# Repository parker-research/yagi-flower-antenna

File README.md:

# yagi-flower-antenna

A group of UHF yagi antennas, arranged in a flower pattern and connected with a SP8T RF switch, to enable coarse beam direction control (like an antenna rotator, but solid-state).

The technical name for this not-all-that-novel approach is "faceted/switched-element array".

## Status

In development. Expected completion: 2026-12-01.

## Parts

1. Antennas (6x yagi antennas, approx. 7 dBi each)
2. Structural mount for antennas (see [`mechanical/`](mechanical/README.md))
3. SP8T RF switch PCB
    - Microcontroller
    - SP8T RF switch IC (SKY13418)
    - LNAs between each antenna port and the RF switch
    - SMA ports to each antenna + common
    - 3D-printed enclosure (see [`mechanical/`](mechanical/README.md))
4. Firmware for PCB microcontroller, masquerading as an antenna rotator (see [`firmware/`](firmware/README.md))
5. Cables to each antenna

## Why?

Satellite tracking works best with a directional antenna: less ambient noise/interference, and higher gain.

However, mechanical antenna rotators are expensive and wear out over time. They require zeroing/calibration, especially after power outages. There are no high-quality open source/DIY designs available. Cheap rotators (e.g., AntRunner) fail in weatherproofing.

This project aims to solve these problems by providing a low-cost, high-quality, open source/DIY, solid-state replacement for a traditional mechanical antenna rotator.

Consider an antenna being deployed in a remote location, like the arctic. As far as I can tell, this yagi flower antenna is ideal for such a deployment. And, an omnidirectional antenna might be almost as much work to build as this project is.

## Features

- Downlink-only
- Presents itself as a traditional antenna rotator, ensuring compatibility with existing antenna rotator software (e.g., SatNOGS Client, GPredict)
- Solid-state (no moving parts) adds reliability and durability for harsh environments

## Related Projects

### Research Papers

- "Concept of 3D Antenna Array for Sub-GHz Rotator-Less Small Satellite Ground Stations and Advanced IoT Gateways": https://www.mdpi.com/2673-4001/6/4/92 / https://doi.org/10.3390/telecom6040092

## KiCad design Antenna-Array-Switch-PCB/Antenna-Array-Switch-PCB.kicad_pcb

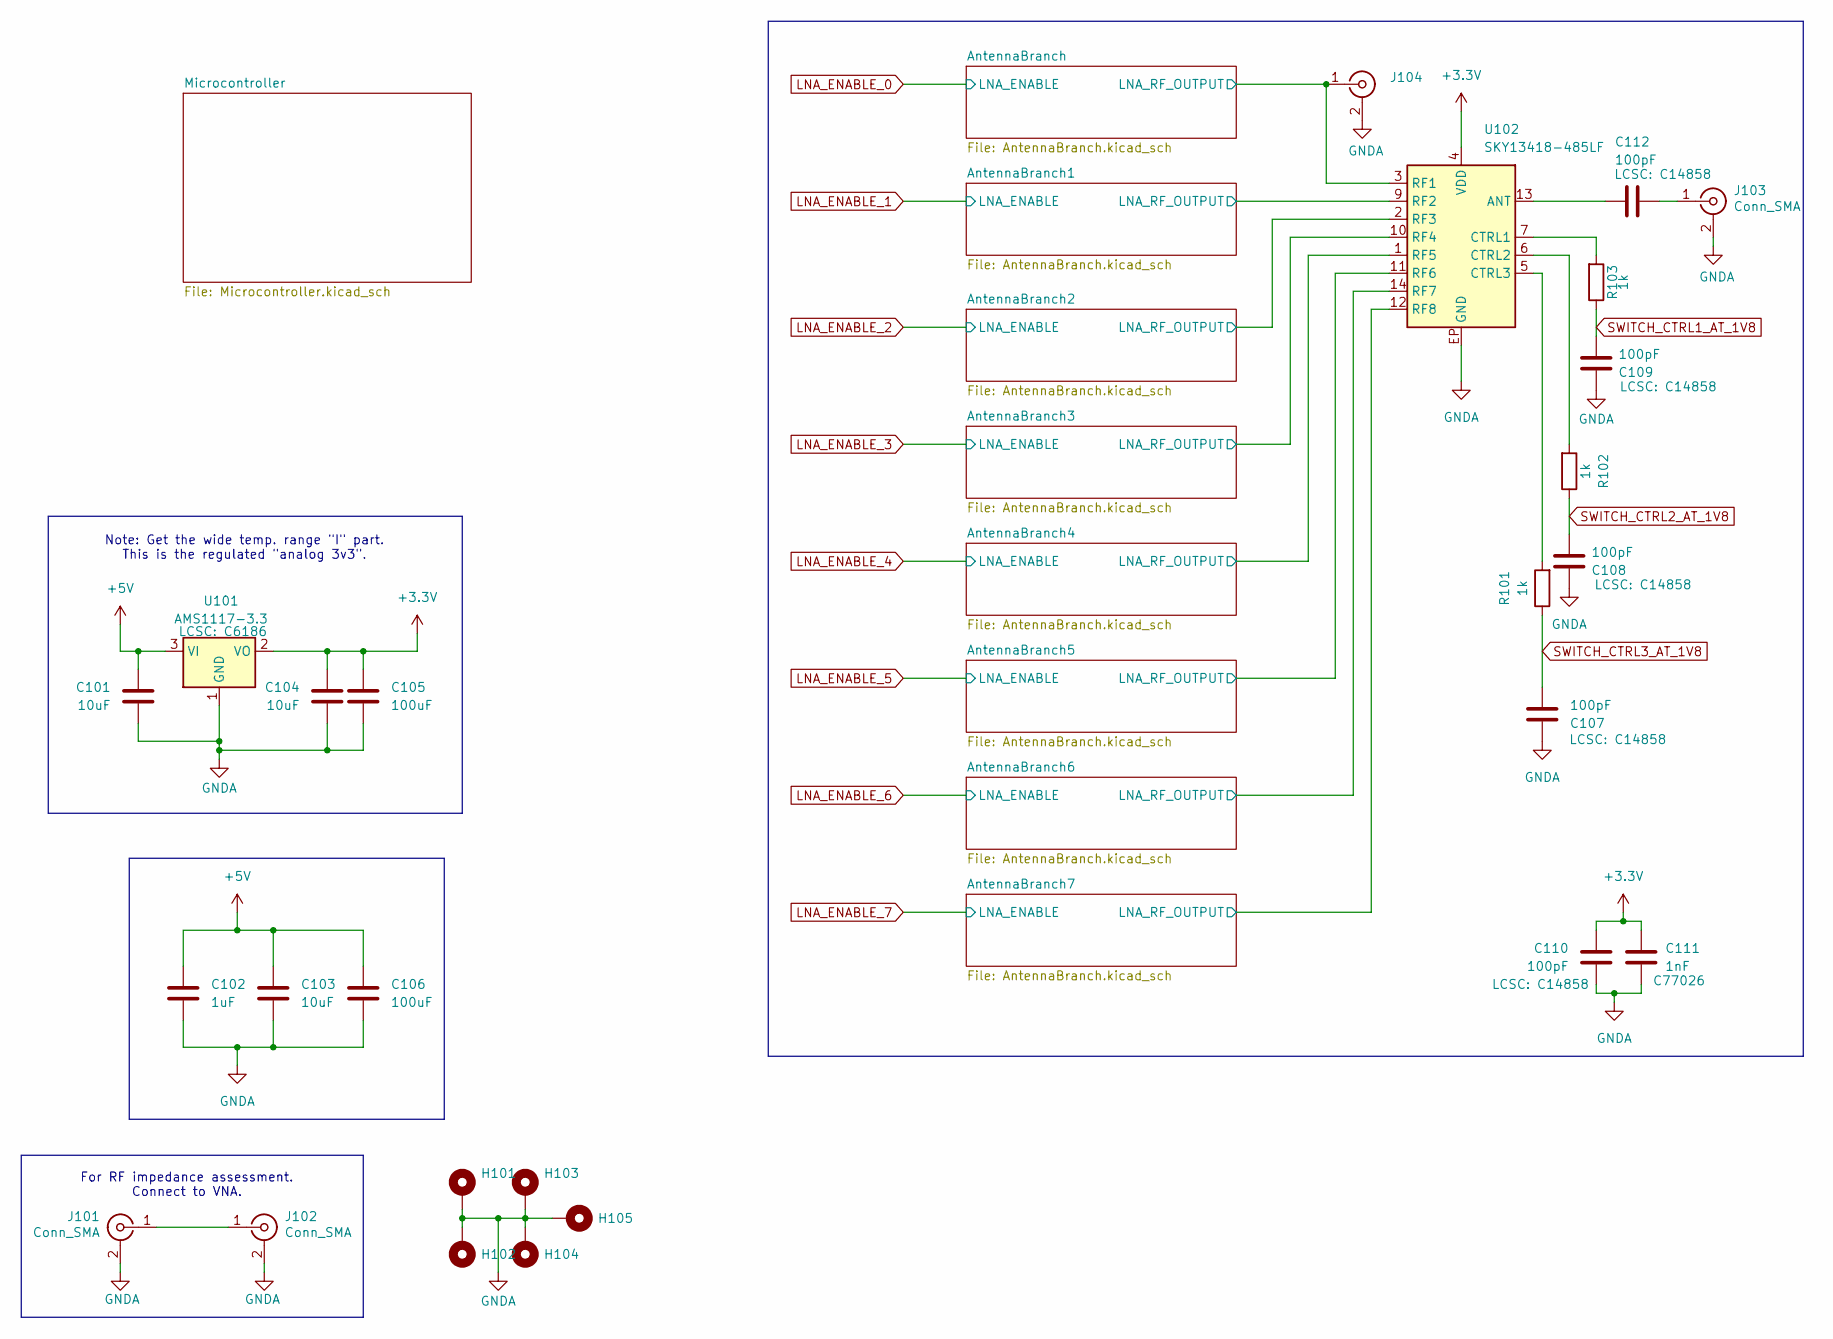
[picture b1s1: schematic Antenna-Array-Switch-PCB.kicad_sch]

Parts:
C101, C103, C104: 10uF; C_1206_3216Metric_Pad1.33x1.80mm_HandSolder
C102: 1uF; C_0603_1608Metric_Pad1.08x0.95mm_HandSolder
C105, C106: 100uF; C_1206_3216Metric_Pad1.33x1.80mm_HandSolder
C107, C108, C109, C110, C112: 100pF; C_0603_1608Metric_Pad1.08x0.95mm_HandSolder; LCSC C14858
C111: 1nF; C_0603_1608Metric_Pad1.08x0.95mm_HandSolder; LCSC C77026
H101, H102, H103, H104, H105: MountingHole_Pad; MountingHole_3.2mm_M3_Pad
J101, J102, J103: Conn_SMA; SMA_Amphenol_901-144_Vertical
J104: Conn_Coaxial; SMA_Amphenol_901-144_Vertical
R101, R102, R103: 1k; R_0603_1608Metric_Pad0.98x0.95mm_HandSolder
U101: AMS1117-3.3; SOT-223-3_TabPin2; LCSC C6186
U102: SKY13418-485LF; Skyworks_QFN-14-1EP_2x2mm_SKY13418_Handsolder; LCSC C150871

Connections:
+3.3V: C104.1, C105.1, C110.2, C111.2, U101.2 (VO), U102.4 (VDD)
+5V: C101.1, C102.1, C103.1, C106.1, U101.3 (VI); also elsewhere on the board
/AntennaBranch1/LNA_RF_OUTPUT: U102.9 (RF2); also elsewhere on the board
/AntennaBranch2/LNA_RF_OUTPUT: U102.2 (RF3); also elsewhere on the board
/AntennaBranch3/LNA_RF_OUTPUT: U102.10 (RF4); also elsewhere on the board
/AntennaBranch4/LNA_RF_OUTPUT: U102.1 (RF5); also elsewhere on the board
/AntennaBranch5/LNA_RF_OUTPUT: U102.11 (RF6); also elsewhere on the board
/AntennaBranch6/LNA_RF_OUTPUT: U102.14 (RF7); also elsewhere on the board
/AntennaBranch7/LNA_RF_OUTPUT: U102.12 (RF8); also elsewhere on the board
/AntennaBranch/LNA_RF_OUTPUT: J104.1 (In), U102.3 (RF1); also elsewhere on the board
GNDA: C101.2, C102.2, C103.2, C104.2, C105.2, C106.2, C107.2, C108.2, C109.2, C110.1, C111.1, H101.1 (1_1), H102.1 (1_1), H103.1 (1_1), H104.1 (1_1), H105.1 (1_1), J101.2 (Ext), J102.2 (Ext), J103.2 (Ext), J104.2 (Ext), U101.1 (GND), U102.EP (GND); also elsewhere on the board
unnamed: J101.1 (In), J102.1 (In)
unnamed: C112.1, J103.1 (In)
unnamed: C112.2, U102.13 (ANT)
unnamed: R103.2, U102.7 (CTRL1)
unnamed: R102.2, U102.6 (CTRL2)
unnamed: R101.2, U102.5 (CTRL3)
SWITCH_CTRL1_AT_1V8: C109.1, R103.1; also elsewhere on the board
SWITCH_CTRL2_AT_1V8: C108.1, R102.1; also elsewhere on the board
SWITCH_CTRL3_AT_1V8: C107.1, R101.1; also elsewhere on the board

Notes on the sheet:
For RF impedance assessment. Connect to VNA.
Note: Get the wide temp. range "I" part. This is the regulated "analog 3v3".

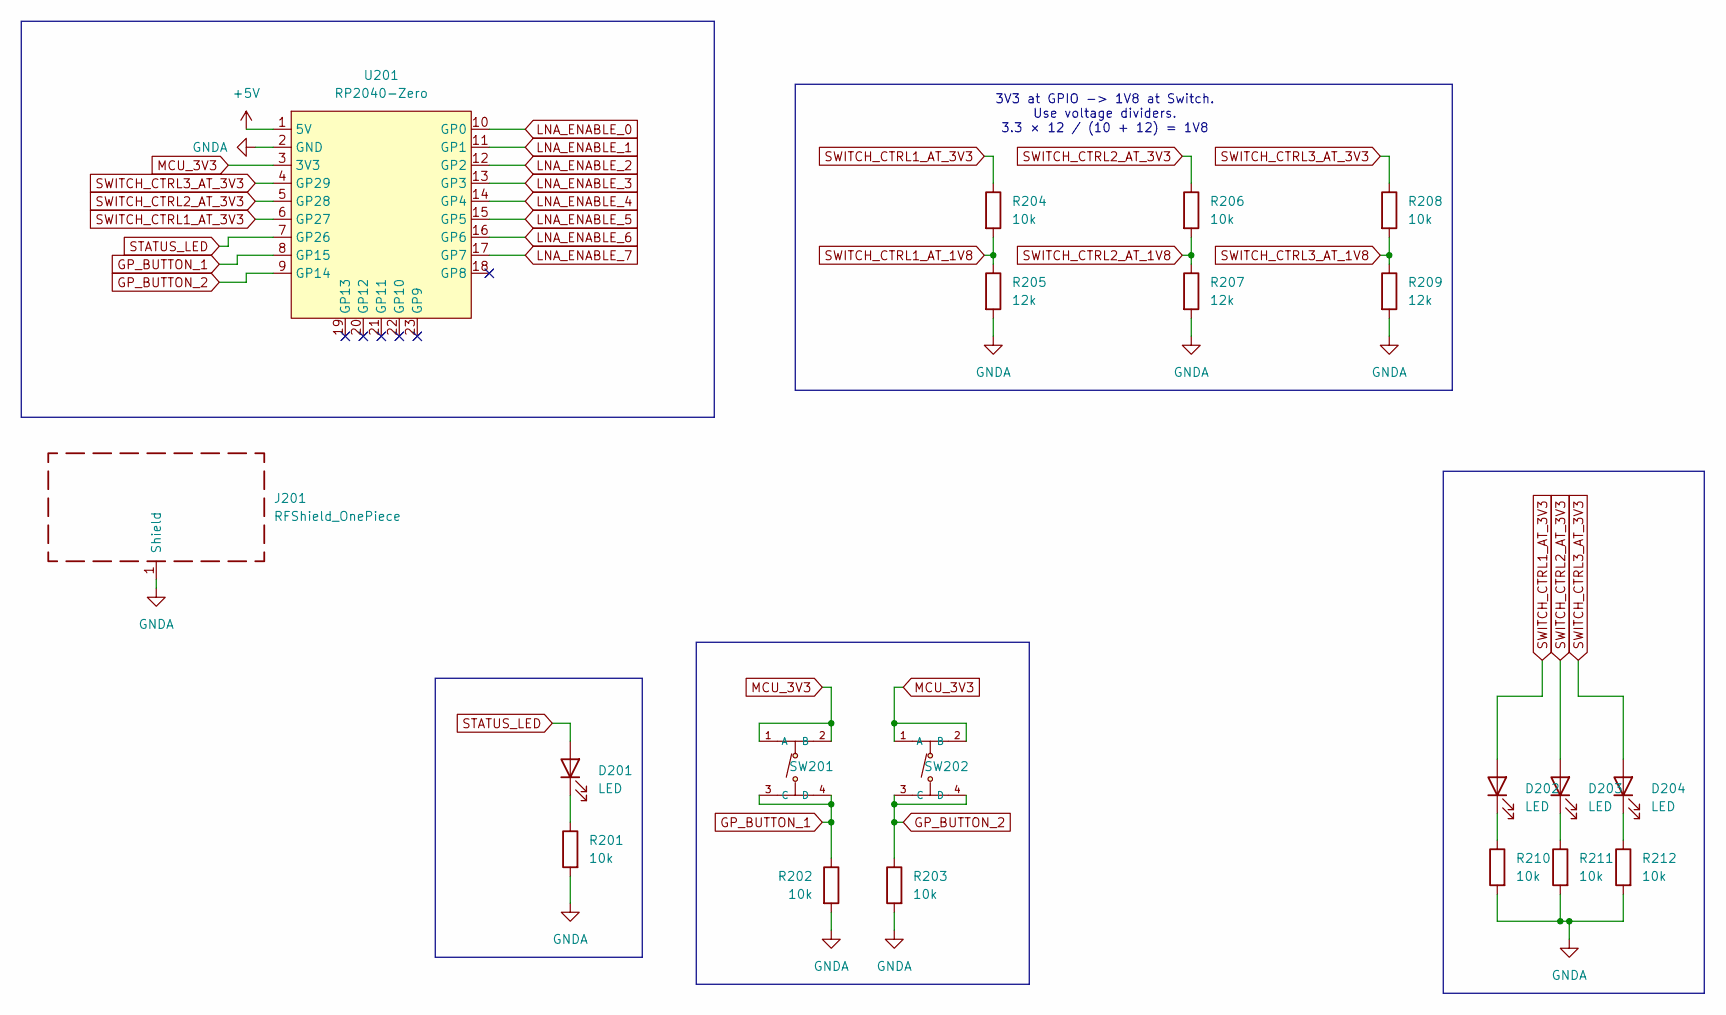
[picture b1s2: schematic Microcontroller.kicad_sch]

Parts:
D201, D202, D203, D204: LED; LED_0603_1608Metric_Pad1.05x0.95mm_HandSolder
J201: RFShield_OnePiece; Wuerth_36103305_30x30mm
R201, R202, R203, R204, R206, R208, R210, R211, R212: 10k; R_0603_1608Metric_Pad0.98x0.95mm_HandSolder
R205, R207, R209: 12k; R_0603_1608Metric_Pad0.98x0.95mm_HandSolder
SW201, SW202: TS-1187A-B-A-B; C318884_SW-SMD_4P-L5_1-W5_1-P3_70-LS6_5-TL_H1_5; LCSC C318884
U201: RP2040-Zero; RP2040 Zero

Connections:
+5V: U201.1 (5V); also elsewhere on the board
GNDA: J201.1 (Shield_1), R201.2, R202.2, R203.2, R205.2, R207.2, R209.2, R210.2, R211.2, R212.2, U201.2 (GND); also elsewhere on the board
GP_BUTTON_1: R202.1, SW201.3 (C), SW201.4 (D), U201.8 (GP15)
GP_BUTTON_2: R203.1, SW202.3 (C), SW202.4 (D), U201.9 (GP14)
LNA_ENABLE_0: U201.10 (GP0); also elsewhere on the board
LNA_ENABLE_1: U201.11 (GP1); also elsewhere on the board
LNA_ENABLE_2: U201.12 (GP2); also elsewhere on the board
LNA_ENABLE_3: U201.13 (GP3); also elsewhere on the board
LNA_ENABLE_4: U201.14 (GP4); also elsewhere on the board
LNA_ENABLE_5: U201.15 (GP5); also elsewhere on the board
LNA_ENABLE_6: U201.16 (GP6); also elsewhere on the board
LNA_ENABLE_7: U201.17 (GP7); also elsewhere on the board
MCU_3V3: SW201.1 (A), SW201.2 (B), SW202.1 (A), SW202.2 (B), U201.3 (3V3)
unnamed: D201.1 (K), R201.1
unnamed: D202.1 (K), R210.1
unnamed: D203.1 (K), R211.1
unnamed: D204.1 (K), R212.1
STATUS_LED: D201.2 (A), U201.7 (GP26)
SWITCH_CTRL1_AT_1V8: R204.2, R205.1; also elsewhere on the board
SWITCH_CTRL1_AT_3V3: D202.2 (A), R204.1, U201.6 (GP27)
SWITCH_CTRL2_AT_1V8: R206.2, R207.1; also elsewhere on the board
SWITCH_CTRL2_AT_3V3: D203.2 (A), R206.1, U201.5 (GP28)
SWITCH_CTRL3_AT_1V8: R208.2, R209.1; also elsewhere on the board
SWITCH_CTRL3_AT_3V3: D204.2 (A), R208.1, U201.4 (GP29)

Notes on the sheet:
3V3 at GPIO -> 1V8 at Switch. Use voltage dividers. 3.3 × 12 / (10 + 12) = 1V8

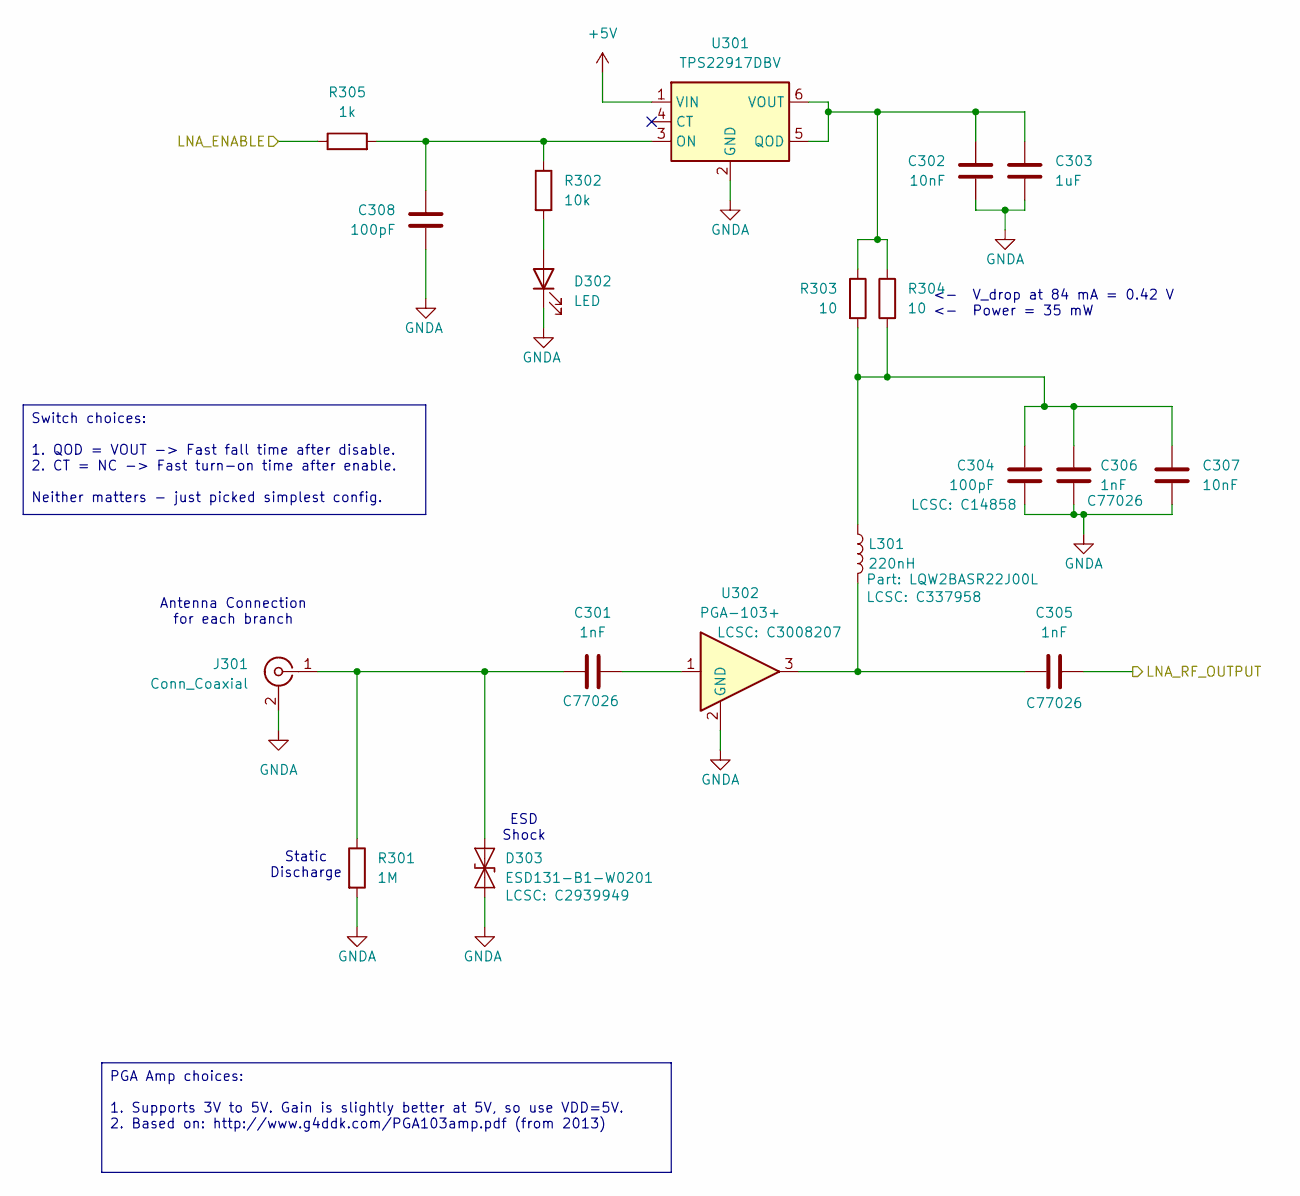
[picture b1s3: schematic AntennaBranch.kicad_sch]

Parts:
C301, C305, C306: 1nF; C_0603_1608Metric_Pad1.08x0.95mm_HandSolder; LCSC C77026
C302, C307: 10nF; C_0603_1608Metric_Pad1.08x0.95mm_HandSolder
C303: 1uF; C_0603_1608Metric_Pad1.08x0.95mm_HandSolder
C304: 100pF; C_0603_1608Metric_Pad1.08x0.95mm_HandSolder; LCSC C14858
C308: 100pF; C_0603_1608Metric_Pad1.08x0.95mm_HandSolder
D302: LED; LED_0603_1608Metric_Pad1.05x0.95mm_HandSolder
D303: ESD131-B1-W0201; Infineon_SG-WLL-2-3_0.58x0.28_P0.36mm; LCSC C2939949
J301: Conn_Coaxial; SMA_Amphenol_901-144_Vertical
L301: 220nH; L_0805_2012Metric_Pad1.05x1.20mm_HandSolder; Part LQW2BASR22J00L; LCSC C337958
R301: 1M; R_0603_1608Metric_Pad0.98x0.95mm_HandSolder
R302: 10k; R_0603_1608Metric_Pad0.98x0.95mm_HandSolder
R303, R304: 10; R_0603_1608Metric_Pad0.98x0.95mm_HandSolder
R305: 1k; R_0603_1608Metric_Pad0.98x0.95mm_HandSolder
U301: TPS22917DBV; SOT-23-6
U302: PGA-103+; SOT-89-3; LCSC C3008207

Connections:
+5V: U301.1 (VIN); also elsewhere on the board
/AntennaBranch/LNA_RF_OUTPUT: C305.2; also elsewhere on the board
GNDA: C302.1, C303.1, C304.1, C306.1, C307.1, C308.1, D302.1 (K), D303.1 (A1), J301.2 (Ext), R301.2, U301.2 (GND), U302.2 (GND_2); also elsewhere on the board
LNA_ENABLE_0: R305.1; also elsewhere on the board
unnamed: C301.2, U302.1
unnamed: C304.2, C306.2, C307.2, L301.1, R303.2, R304.2
unnamed: C305.1, L301.2, U302.3
unnamed: D302.2 (A), R302.2
unnamed: C301.1, D303.2 (A2), J301.1 (In), R301.1
unnamed: C308.2, R302.1, R305.2, U301.3 (ON)
unnamed: C302.2, C303.2, R303.1, R304.1, U301.5 (QOD), U301.6 (VOUT)

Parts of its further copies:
C401, C405, C406, C501, C505, C506, C601, C605, C606, C701, C705, C706, C801, C805, C806, C901, C905, C906, C1001, C1005, C1006: 1nF; C_0603_1608Metric_Pad1.08x0.95mm_HandSolder; LCSC C77026
C402, C407, C502, C507, C602, C607, C702, C707, C802, C807, C902, C907, C1002, C1007: 10nF; C_0603_1608Metric_Pad1.08x0.95mm_HandSolder
C403, C503, C603, C703, C803, C903, C1003: 1uF; C_0603_1608Metric_Pad1.08x0.95mm_HandSolder
C404, C504, C604, C704, C804, C904, C1004: 100pF; C_0603_1608Metric_Pad1.08x0.95mm_HandSolder; LCSC C14858
C408, C508, C608, C708, C808, C908, C1008: 100pF; C_0603_1608Metric_Pad1.08x0.95mm_HandSolder
D402, D502, D602, D702, D802, D902, D1002: LED; LED_0603_1608Metric_Pad1.05x0.95mm_HandSolder
D403, D503, D603, D703, D803, D903, D1003: ESD131-B1-W0201; Infineon_SG-WLL-2-3_0.58x0.28_P0.36mm; LCSC C2939949
J401, J501, J601, J701, J801, J901, J1001: Conn_Coaxial; SMA_Amphenol_901-144_Vertical
L401, L501, L601, L701, L801, L901, L1001: 220nH; L_0805_2012Metric_Pad1.05x1.20mm_HandSolder; Part LQW2BASR22J00L; LCSC C337958
R401, R501, R601, R701, R801, R901, R1001: 1M; R_0603_1608Metric_Pad0.98x0.95mm_HandSolder
R402, R502, R602, R702, R802, R902, R1002: 10k; R_0603_1608Metric_Pad0.98x0.95mm_HandSolder
R403, R404, R503, R504, R603, R604, R703, R704, R803, R804, R903, R904, R1003, R1004: 10; R_0603_1608Metric_Pad0.98x0.95mm_HandSolder
R405, R505, R605, R705, R805, R905, R1005: 1k; R_0603_1608Metric_Pad0.98x0.95mm_HandSolder
U401, U501, U601, U701, U801, U901, U1001: TPS22917DBV; SOT-23-6
U402, U502, U602, U702, U802, U902, U1002: PGA-103+; SOT-89-3; LCSC C3008207

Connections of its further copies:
+5V: U401.1 (VIN), U501.1 (VIN), U601.1 (VIN), U701.1 (VIN), U801.1 (VIN), U901.1 (VIN), U1001.1 (VIN); also elsewhere on the board
/AntennaBranch1/LNA_RF_OUTPUT: C405.2; also elsewhere on the board
/AntennaBranch2/LNA_RF_OUTPUT: C505.2; also elsewhere on the board
/AntennaBranch3/LNA_RF_OUTPUT: C605.2; also elsewhere on the board
/AntennaBranch4/LNA_RF_OUTPUT: C705.2; also elsewhere on the board
/AntennaBranch5/LNA_RF_OUTPUT: C805.2; also elsewhere on the board
/AntennaBranch6/LNA_RF_OUTPUT: C905.2; also elsewhere on the board
/AntennaBranch7/LNA_RF_OUTPUT: C1005.2; also elsewhere on the board
GNDA: C402.1, C403.1, C404.1, C406.1, C407.1, C408.1, C502.1, C503.1, C504.1, C506.1, C507.1, C508.1, C602.1, C603.1, C604.1, C606.1, C607.1, C608.1, C702.1, C703.1, C704.1, C706.1, C707.1, C708.1, C802.1, C803.1, C804.1, C806.1, C807.1, C808.1, C902.1, C903.1, C904.1, C906.1, C907.1, C908.1, C1002.1, C1003.1, C1004.1, C1006.1, C1007.1, C1008.1, D402.1 (K), D403.1 (A1), D502.1 (K), D503.1 (A1), D602.1 (K), D603.1 (A1), D702.1 (K), D703.1 (A1), D802.1 (K), D803.1 (A1), D902.1 (K), D903.1 (A1), D1002.1 (K), D1003.1 (A1), J401.2 (Ext), J501.2 (Ext), J601.2 (Ext), J701.2 (Ext), J801.2 (Ext), J901.2 (Ext), J1001.2 (Ext), R401.2, R501.2, R601.2, R701.2, R801.2, R901.2, R1001.2, U401.2 (GND), U402.2 (GND_2), U501.2 (GND), U502.2 (GND_2), U601.2 (GND), U602.2 (GND_2), U701.2 (GND), U702.2 (GND_2), U801.2 (GND), U802.2 (GND_2), U901.2 (GND), U902.2 (GND_2), U1001.2 (GND), U1002.2 (GND_2); also elsewhere on the board
LNA_ENABLE_1: R405.1; also elsewhere on the board
LNA_ENABLE_2: R505.1; also elsewhere on the board
LNA_ENABLE_3: R605.1; also elsewhere on the board
LNA_ENABLE_4: R705.1; also elsewhere on the board
LNA_ENABLE_5: R805.1; also elsewhere on the board
LNA_ENABLE_6: R905.1; also elsewhere on the board
LNA_ENABLE_7: R1005.1; also elsewhere on the board
unnamed: C401.2, U402.1
unnamed: C404.2, C406.2, C407.2, L401.1, R403.2, R404.2
unnamed: C405.1, L401.2, U402.3
unnamed: C501.2, U502.1
unnamed: C504.2, C506.2, C507.2, L501.1, R503.2, R504.2
unnamed: C505.1, L501.2, U502.3
unnamed: C601.2, U602.1
unnamed: C604.2, C606.2, C607.2, L601.1, R603.2, R604.2
unnamed: C605.1, L601.2, U602.3
unnamed: C701.2, U702.1
unnamed: C704.2, C706.2, C707.2, L701.1, R703.2, R704.2
unnamed: C705.1, L701.2, U702.3
unnamed: C801.2, U802.1
unnamed: C804.2, C806.2, C807.2, L801.1, R803.2, R804.2
unnamed: C805.1, L801.2, U802.3
unnamed: C901.2, U902.1
unnamed: C904.2, C906.2, C907.2, L901.1, R903.2, R904.2
unnamed: C905.1, L901.2, U902.3
unnamed: C1001.2, U1002.1
unnamed: C1004.2, C1006.2, C1007.2, L1001.1, R1003.2, R1004.2
unnamed: C1005.1, L1001.2, U1002.3
unnamed: D402.2 (A), R402.2
unnamed: C401.1, D403.2 (A2), J401.1 (In), R401.1
unnamed: D502.2 (A), R502.2
unnamed: C501.1, D503.2 (A2), J501.1 (In), R501.1
unnamed: D602.2 (A), R602.2
unnamed: C601.1, D603.2 (A2), J601.1 (In), R601.1
unnamed: D702.2 (A), R702.2
unnamed: C701.1, D703.2 (A2), J701.1 (In), R701.1
unnamed: D802.2 (A), R802.2
unnamed: C801.1, D803.2 (A2), J801.1 (In), R801.1
unnamed: D902.2 (A), R902.2
unnamed: C901.1, D903.2 (A2), J901.1 (In), R901.1
unnamed: D1002.2 (A), R1002.2
unnamed: C1001.1, D1003.2 (A2), J1001.1 (In), R1001.1
unnamed: C408.2, R402.1, R405.2, U401.3 (ON)
unnamed: C402.2, C403.2, R403.1, R404.1, U401.5 (QOD), U401.6 (VOUT)
unnamed: C508.2, R502.1, R505.2, U501.3 (ON)
unnamed: C502.2, C503.2, R503.1, R504.1, U501.5 (QOD), U501.6 (VOUT)
unnamed: C608.2, R602.1, R605.2, U601.3 (ON)
unnamed: C602.2, C603.2, R603.1, R604.1, U601.5 (QOD), U601.6 (VOUT)
unnamed: C708.2, R702.1, R705.2, U701.3 (ON)
unnamed: C702.2, C703.2, R703.1, R704.1, U701.5 (QOD), U701.6 (VOUT)
unnamed: C808.2, R802.1, R805.2, U801.3 (ON)
unnamed: C802.2, C803.2, R803.1, R804.1, U801.5 (QOD), U801.6 (VOUT)
unnamed: C908.2, R902.1, R905.2, U901.3 (ON)
unnamed: C902.2, C903.2, R903.1, R904.1, U901.5 (QOD), U901.6 (VOUT)
unnamed: C1008.2, R1002.1, R1005.2, U1001.3 (ON)
unnamed: C1002.2, C1003.2, R1003.1, R1004.1, U1001.5 (QOD), U1001.6 (VOUT)

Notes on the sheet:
Static Discharge
<- V_drop at 84 mA = 0.42 V <- Power = 35 mW
ESD Shock
Antenna Connection for each branch
Switch choices: 1. QOD = VOUT -> Fast fall time after disable. 2. CT = NC -> Fast turn-on time after enable. Neither matters - just picked simplest config.
PGA Amp choices: 1. Supports 3V to 5V. Gain is slightly better at 5V, so use VDD=5V. 2. Based on: http://www.g4ddk.com/PGA103amp.pdf (from 2013)

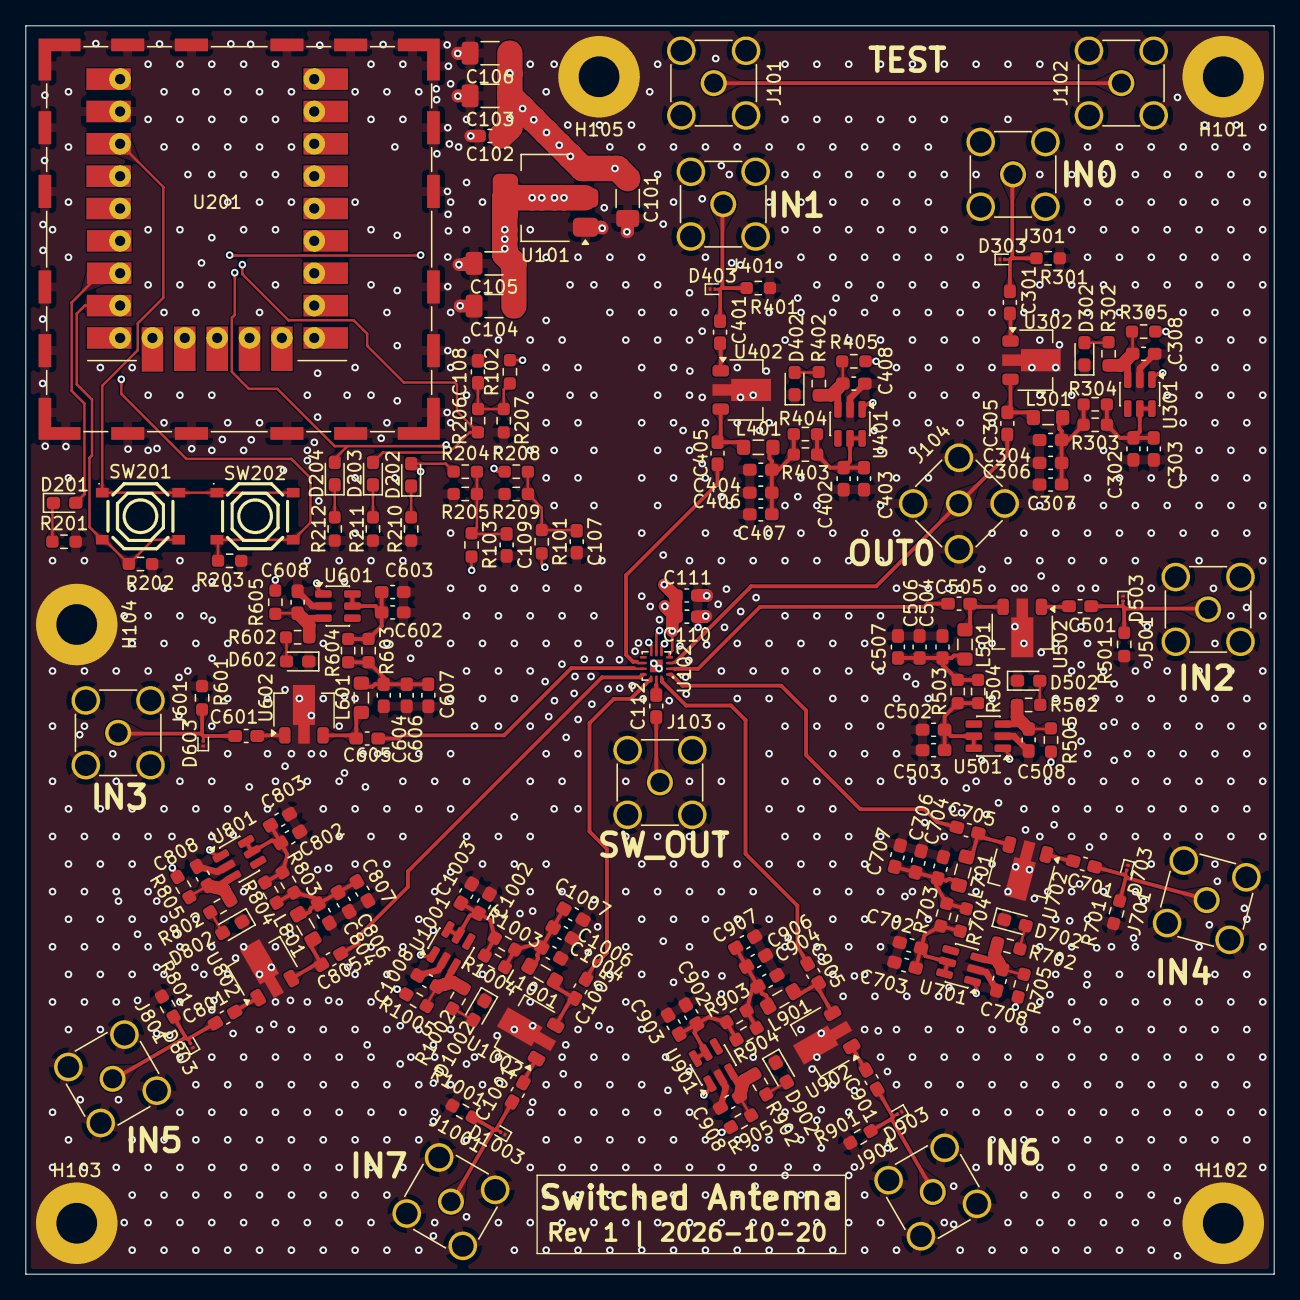
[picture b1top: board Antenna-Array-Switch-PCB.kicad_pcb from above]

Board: 4 copper layers, 98.0 x 98.0 mm, 198 parts (0 on the bottom side), 95 nets.
